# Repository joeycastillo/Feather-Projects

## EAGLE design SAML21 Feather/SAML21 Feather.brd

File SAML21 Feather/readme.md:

# SAML21 Feather

Abandoned halfway through. The useful thing here would be the battery backup for the RTC. 

An interesting idea, but ultimately the SAMD series is so well supported I went back to designing a SAMD board with a battery-backed RTC.

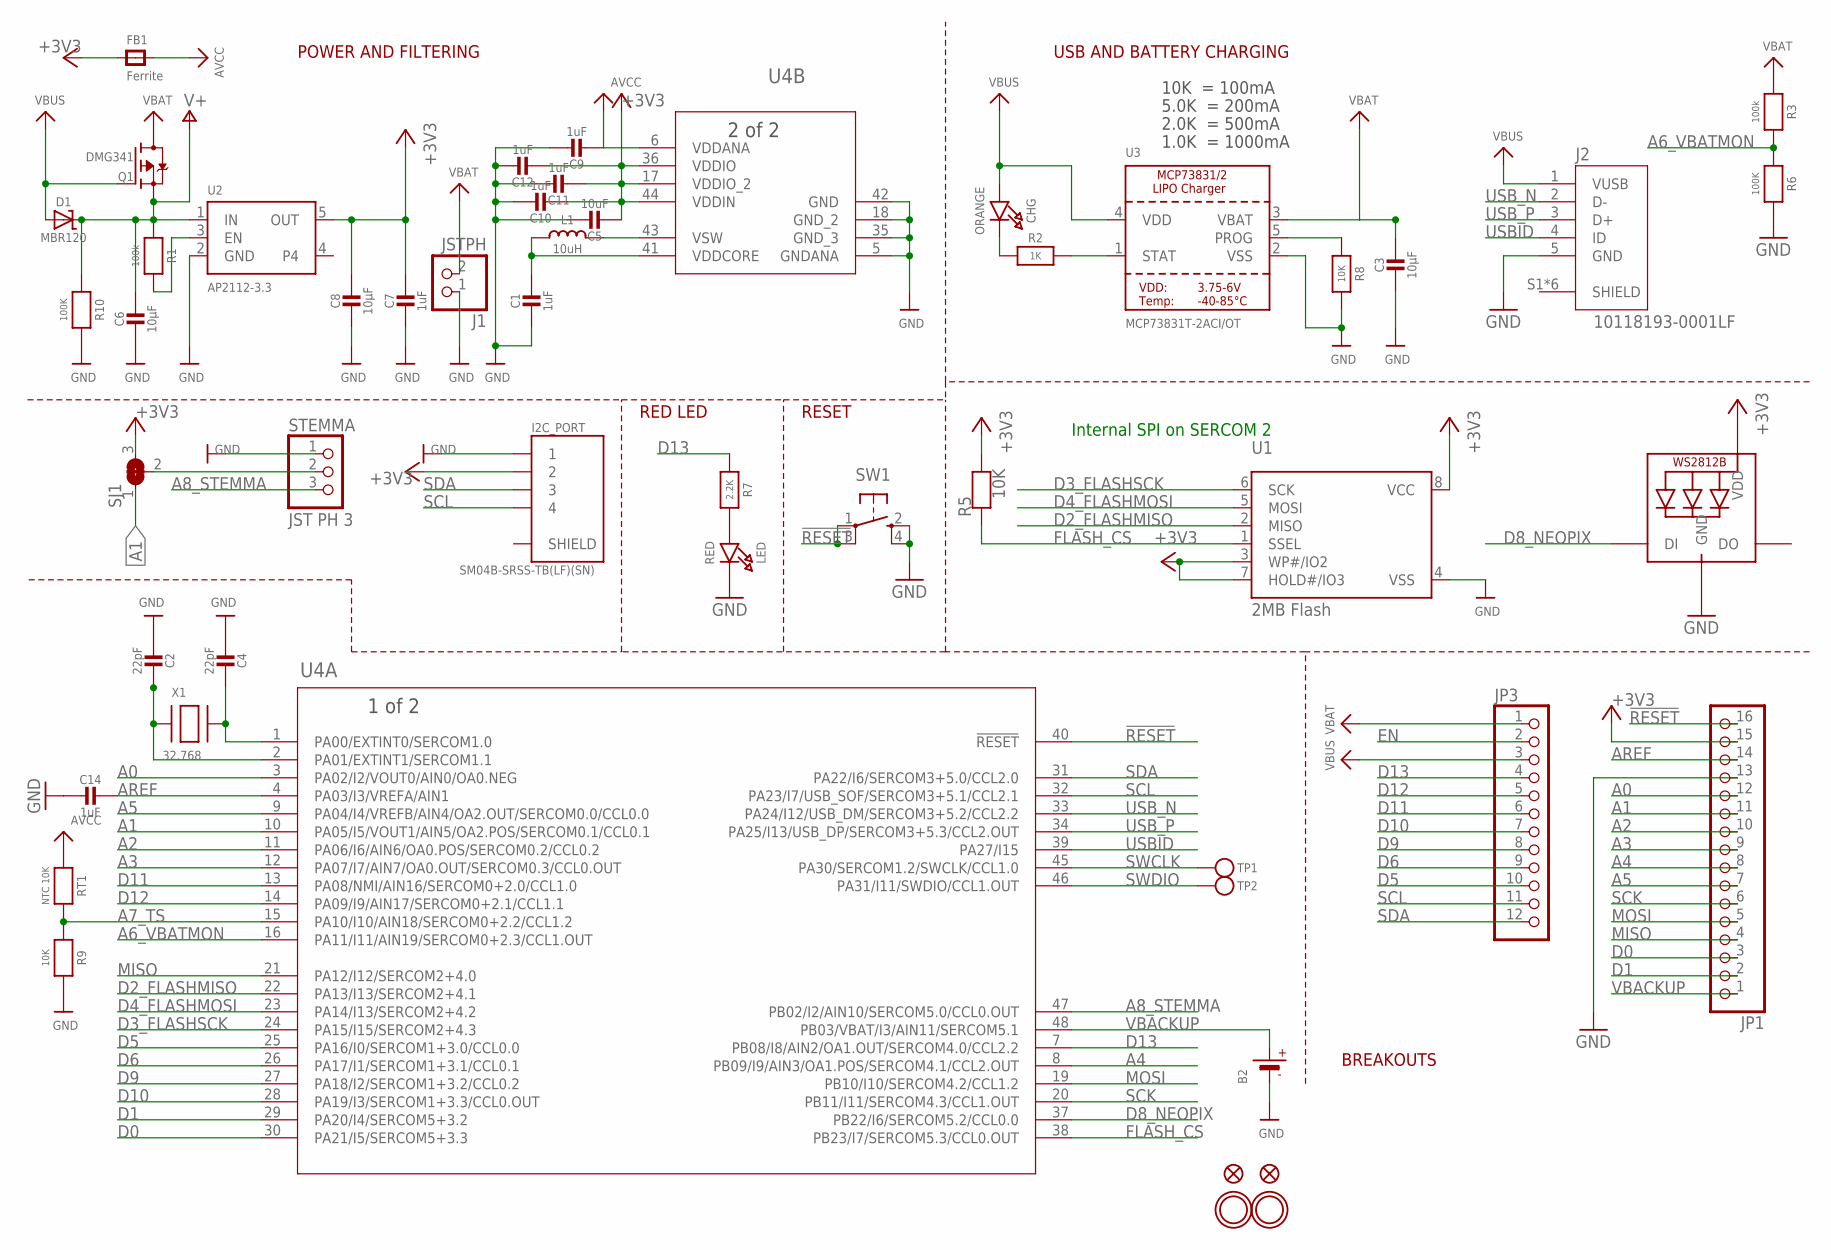
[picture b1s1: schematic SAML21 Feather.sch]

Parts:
B2: CR1220; CR1220-2
C1, C7, C9, C10, C11, C12, C14: 1uF; 0805-NO
C2, C4: 22pF; 0805-NO
C3, C6, C8: 10µF; 0805-NO
C5: 10uF; 0805-NO
CHG: ORANGE; CHIPLED_0805_NOOUTLINE
D1: MBR120; SOD-123
FB1: Ferrite; 0805
I2C_PORT: SM04B-SRSS-TB(LF)(SN); JST_SM04B-SRSS-TB(LF)(SN)
J1: JSTPH; JSTPH2
J2: 10118193-0001LF; FCI_10118193-0001LF
JP1: HEADER-1X16ROUND; 1X16_ROUND
JP3: HEADER-1X12; 1X12_ROUND
L1: 10uH; MICROBUILDER_INDUCTOR_4X4MM_NR401_BIGPADS
LED: RED; CHIPLED_0805_NOOUTLINE
NEOPIX: WS2812B3535; LED3535
Q1: DMG341; SOT23-R
R1: 100k; 0805-NO
R2: 1K; 0805-NO
R3: 100k; 0805_10MGAP
R5, R8, R9: 10K; 0805-NO
R6, R10: 100K; 0805-NO
R7: 2.2K; 0805-NO
RT1: NTC 10K; 0805-NO
SJ1: SOLDERJUMPER_2WAY; SOLDERJUMPER_2WAY_OPEN_NOPASTE
STEMMA: JST PH 3; JSTPH3
SW1: SPST_TACT-KMR2; KMR2
TP1, TP2: TESTPOINTROUND1.5MM; TESTPOINT_ROUND_1.5MM
U1: 2MB Flash; SOIC8_208MIL
U2: AP2112-3.3; SOT23-5
U3: MCP73831T-2ACI/OT; SOT23-5
U4: ATSAML21G16B-ANT; TQFP48_7X7MC
U$31, U$32: MOUNTINGHOLE2.5; MOUNTINGHOLE_2.5_PLATED
U$34, U$35: FIDUCIAL""; FIDUCIAL_1MM
X1: 32.768; XTAL3215

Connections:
!RESET: JP1.16, SW1.1, SW1.3 (P1), U4.40 (!RESET)
+3V3: C5.2, C7.1, C8.1, C10.2, C11.2, C12.2, FB1.1, I2C_PORT.2, JP1.15, NEOPIX.2 (VDD), R5.2, SJ1.3, U1.3 (WP#/IO2), U1.7 (HOLD#/IO3), U1.8 (VCC), U2.5 (OUT), U4.17 (VDDIO_2), U4.36 (VDDIO), U4.44 (VDDIN)
A0: JP1.12, U4.3 (PA02/I2/VOUT0/AIN0/OA0.NEG)
A1: JP1.11, SJ1.1, U4.10 (PA05/I5/VOUT1/AIN5/OA2.POS/SERCOM0.1/CC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)
A2: JP1.10, U4.11 (PA06/I6/AIN6/OA0.POS/SERCOM0.2/CCL0.2)
A3: JP1.9, U4.12 (PA07/I7/AIN7/OA0.OUT/SERCOM0.3/CCL0.OUT)
A4: JP1.8, U4.8 (PB09/I9/AIN3/OA1.POS/SERCOM4.1/CCL2.OUT)
A5: JP1.7, U4.9 (PA04/I4/VREFB/AIN4/OA2.OUT/SERCOM0.0/CC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)
A6_VBATMON: R3.2, R6.1, U4.16 (PA11/I11/AIN19/SERCOM0+2.3/CCL1.OUT)
A7_TS: R9.1, RT1.2, U4.15 (PA10/I10/AIN18/SERCOM0+2.2/CCL1.2)
A8_STEMMA: STEMMA.3, U4.47 (PB02/I2/AIN10/SERCOM5.0/CCL0.OUT)
AREF: C14.1, JP1.14, U4.4 (PA03/I3/VREFA/AIN1)
AVCC: C9.2, FB1.2, RT1.1, U4.6 (VDDANA)
D0: JP1.3, U4.30 (PA21/I5/SERCOM5+3.3)
D1: JP1.2, U4.29 (PA20/I4/SERCOM5+3.2)
D2_FLASHMISO: U1.2 (MISO), U4.22 (PA13/I13/SERCOM2+4.1)
D3_FLASHSCK: U1.6 (SCK), U4.24 (PA15/I15/SERCOM2+4.3)
D4_FLASHMOSI: U1.5 (MOSI), U4.23 (PA14/I13/SERCOM2+4.2)
D5: JP3.10, U4.25 (PA16/I0/SERCOM1+3.0/CCL0.0)
D6: JP3.9, U4.26 (PA17/I1/SERCOM1+3.1/CCL0.1)
D8_NEOPIX: NEOPIX.1 (DI), U4.37 (PB22/I6/SERCOM5.2/CCL0.0)
D9: JP3.8, U4.27 (PA18/I2/SERCOM1+3.2/CCL0.2)
D10: JP3.7, U4.28 (PA19/I3/SERCOM1+3.3/CCL0.OUT)
D11: JP3.6, U4.13 (PA08/NMI/AIN16/SERCOM0+2.0/CCL1.0)
D12: JP3.5, U4.14 (PA09/I9/AIN17/SERCOM0+2.1/CCL1.1)
D13: JP3.4, R7.1, U4.7 (PB08/I8/AIN2/OA1.OUT/SERCOM4.0/CCL2.2)
EN: JP3.2, R1.2, U2.3 (EN)
FLASH_CS: R5.1, U1.1 (SSEL), U4.38 (PB23/I7/SERCOM5.3/CCL0.OUT)
GND: B2.-, C1.2, C2.2, C3.2, C4.2, C5.1, C6.2, C7.2, C8.2, C9.1, C10.1, C11.1, C12.1, C14.2, I2C_PORT.1, J1.1, J2.5 (GND), JP1.13, LED.C, NEOPIX.4 (GND), R6.2, R8.2, R9.2, R10.2, STEMMA.1, SW1.2 (S), SW1.4 (S1), U1.4 (VSS), U2.2 (GND), U3.2 (VSS), U4.5 (GNDANA), U4.18 (GND_2), U4.35 (GND_3), U4.42 (GND)
MISO: JP1.4, U4.21 (PA12/I12/SERCOM2+4.0)
MOSI: JP1.5, U4.19 (PB10/I10/SERCOM4.2/CCL1.2)
unnamed: CHG.C, R2.1
unnamed: LED.A, R7.2
unnamed: SJ1.2, STEMMA.2
PROG: R8.1, U3.5 (PROG)
SCK: JP1.6, U4.20 (PB11/I11/SERCOM4.3/CCL1.OUT)
SCL: I2C_PORT.4, JP3.11, U4.32 (PA23/I7/USB_SOF/SERCOM3+5.1/CCL2.1)
SDA: I2C_PORT.3, JP3.12, U4.31 (PA22/I6/SERCOM3+5.0/CCL2.0)
STAT: R2.2, U3.1 (STAT)
SWCLK: TP1.P$1, U4.45 (PA30/SERCOM1.2/SWCLK/CCL1.0)
SWDIO: TP2.P$1, U4.46 (PA31/I11/SWDIO/CCL1.OUT)
USBID: J2.4 (ID), U4.39 (PA27/I15)
USB_N: J2.2 (D-), U4.33 (PA24/I12/USB_DM/SERCOM3+5.2/CCL2.2)
USB_P: J2.3 (D+), U4.34 (PA25/I13/USB_DP/SERCOM3+5.3/CCL2.OUT)
V+: C6.1, D1.C, Q1.2 (S), R1.1, R10.1, U2.1 (IN)
VBACKUP: B2.+, JP1.1, U4.48 (PB03/VBAT/I3/AIN11/SERCOM5.1)
VBAT: C3.1, J1.2, JP3.1, Q1.3 (D), R3.1, U3.3 (VBAT)
VBUS: CHG.A, D1.A, J2.1 (VUSB), JP3.3, Q1.1 (G), U3.4 (VDD)
VDDCORE: C1.1, L1.P$1 (1), U4.41 (VDDCORE)
VSW: L1.P$2 (2), U4.43 (VSW)
XIN32: C4.1, U4.1 (PA00/EXTINT0/SERCOM1.0), X1.P$2
XOUT32: C2.1, U4.2 (PA01/EXTINT1/SERCOM1.1), X1.P$1

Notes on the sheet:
POWER AND FILTERING
RESET
10K = 100mA
5.0K = 200mA
2.0K = 500mA
1.0K = 1000mA
USB AND BATTERY CHARGING
BREAKOUTS
RED LED
Internal SPI on SERCOM 2

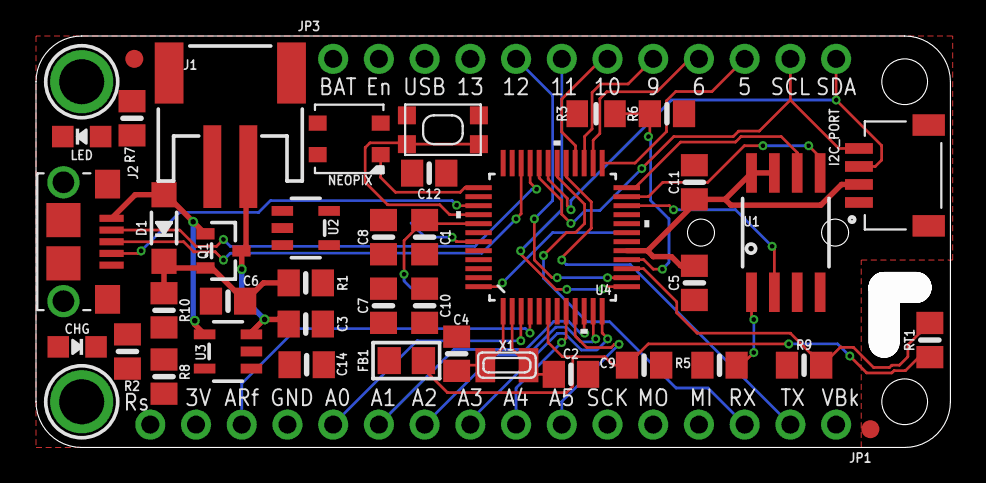
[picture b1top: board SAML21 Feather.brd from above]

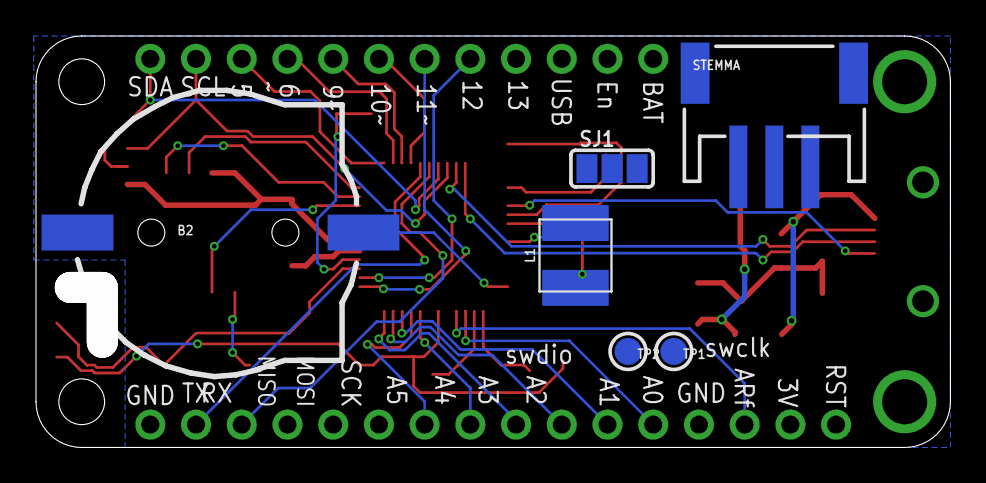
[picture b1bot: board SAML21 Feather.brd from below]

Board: 2 copper layers, 50.8 x 22.9 mm, 50 parts (6 on the bottom side), 52 nets.

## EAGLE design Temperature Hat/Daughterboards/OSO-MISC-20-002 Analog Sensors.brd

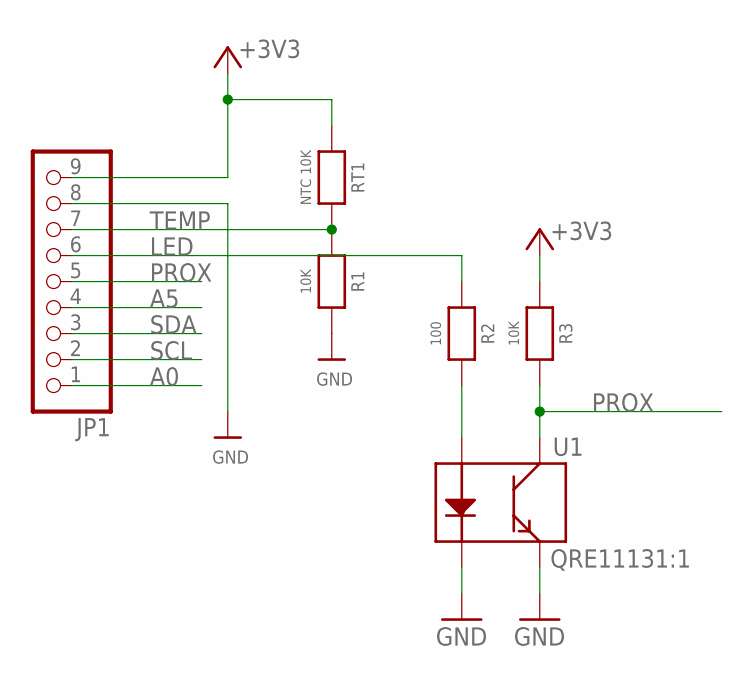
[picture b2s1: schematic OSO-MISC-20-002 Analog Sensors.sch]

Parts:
JP1: HEADER-1X9_JSTSH; JST_SH9
R1, R3: 10K; 0805-NO
R2: 100; 0805-NO
RT1: NTC 10K; 0805-NO
U1: QRE11131:1; QRE1113-1:1

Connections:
+3V3: JP1.9, R3.1, RT1.1
A0: JP1.1
A5: JP1.4
GND: JP1.8, R1.2, U1.2 (K), U1.4 (E)
LED: JP1.6, R2.1
unnamed: R2.2, U1.1 (A)
PROX: JP1.5, R3.2, U1.3 (C)
SCL: JP1.2
SDA: JP1.3
TEMP: JP1.7, R1.1, RT1.2

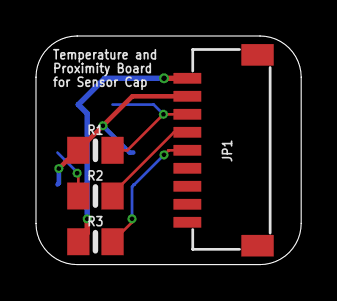
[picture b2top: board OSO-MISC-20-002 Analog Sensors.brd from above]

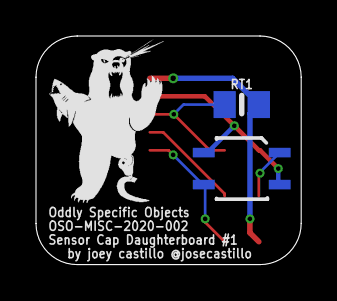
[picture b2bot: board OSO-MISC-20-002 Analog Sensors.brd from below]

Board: 2 copper layers, 14.7 x 12.7 mm, 7 parts (3 on the bottom side), 6 nets.

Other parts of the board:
U$2: OSO_BEAR_250X360MIL_1000DPI

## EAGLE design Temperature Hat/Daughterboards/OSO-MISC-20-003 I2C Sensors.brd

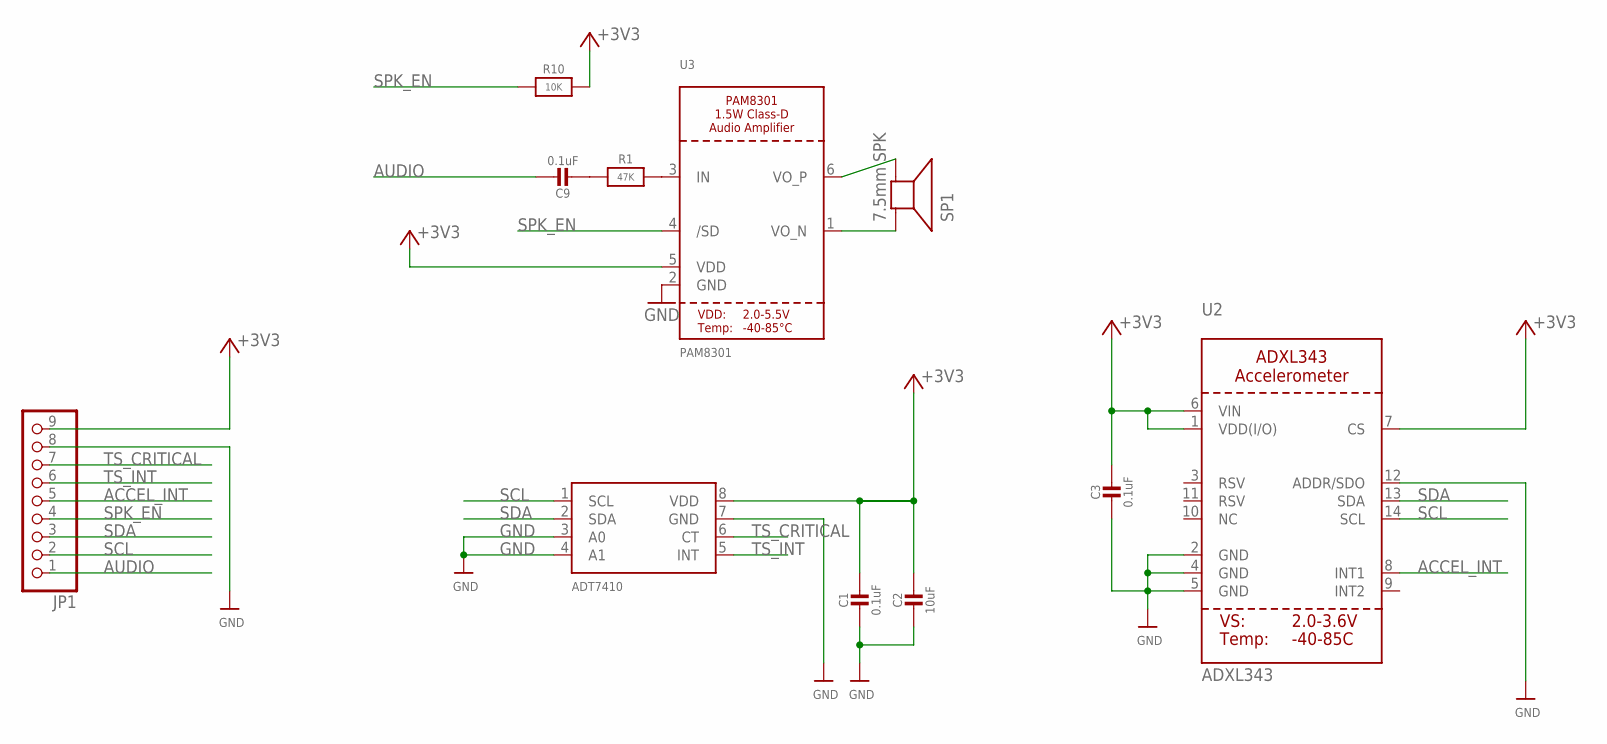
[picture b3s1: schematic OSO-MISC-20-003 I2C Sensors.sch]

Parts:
C1, C3, C9: 0.1uF; 0805-NO
C2: 10uF; 0805-NO
JP1: HEADER-1X9_JSTSH; JST_SH9
R1: 47K; 0805-NO
R10: 10K; 0805-NO
SP1: 7.5mm SPK; BUZZER_SMT_5MM
U1: ADT7410; SOIC8_150MIL
U2: ADXL343; LGA14
U3: PAM8301; SOT23-6

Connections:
+3V3: C1.1, C2.1, C3.1, JP1.9, R10.2, U1.8 (VDD), U2.1 (VDD(I/O)), U2.6 (VIN), U2.7 (CS), U3.5 (VDD)
ACCEL_INT: JP1.5, U2.8 (INT1)
AUDIO: C9.1, JP1.1
GND: C1.2, C2.2, C3.2, JP1.8, U1.3 (A0), U1.4 (A1), U1.7 (GND), U2.2 (GND), U2.4 (GND), U2.5 (GND), U2.12 (ADDR/SDO), U3.2 (GND)
unnamed: C9.2, R1.1
unnamed: R1.2, U3.3 (IN)
SCL: JP1.2, U1.1 (SCL), U2.14 (SCL)
SDA: JP1.3, U1.2 (SDA), U2.13 (SDA)
SPK_EN: JP1.4, R10.1, U3.4 (/SD)
SPK_N: SP1.+, U3.1 (VO_N)
SPK_P: SP1.-, U3.6 (VO_P)
TS_CRITICAL: JP1.7, U1.6 (CT)
TS_INT: JP1.6, U1.5 (INT)

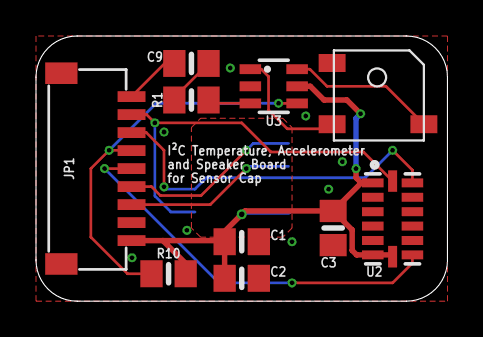
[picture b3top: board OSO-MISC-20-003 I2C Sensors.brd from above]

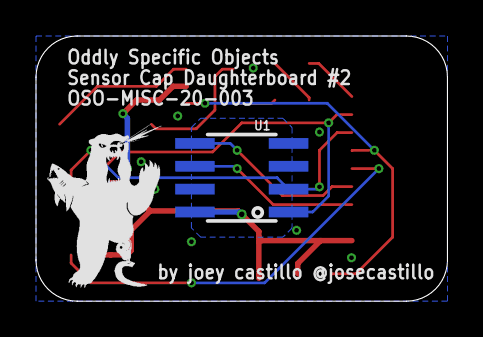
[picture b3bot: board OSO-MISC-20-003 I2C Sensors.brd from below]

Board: 2 copper layers, 22.9 x 14.7 mm, 12 parts (2 on the bottom side), 13 nets.

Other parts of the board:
U$3: OSO_BEAR_250X360MIL_1000DPI

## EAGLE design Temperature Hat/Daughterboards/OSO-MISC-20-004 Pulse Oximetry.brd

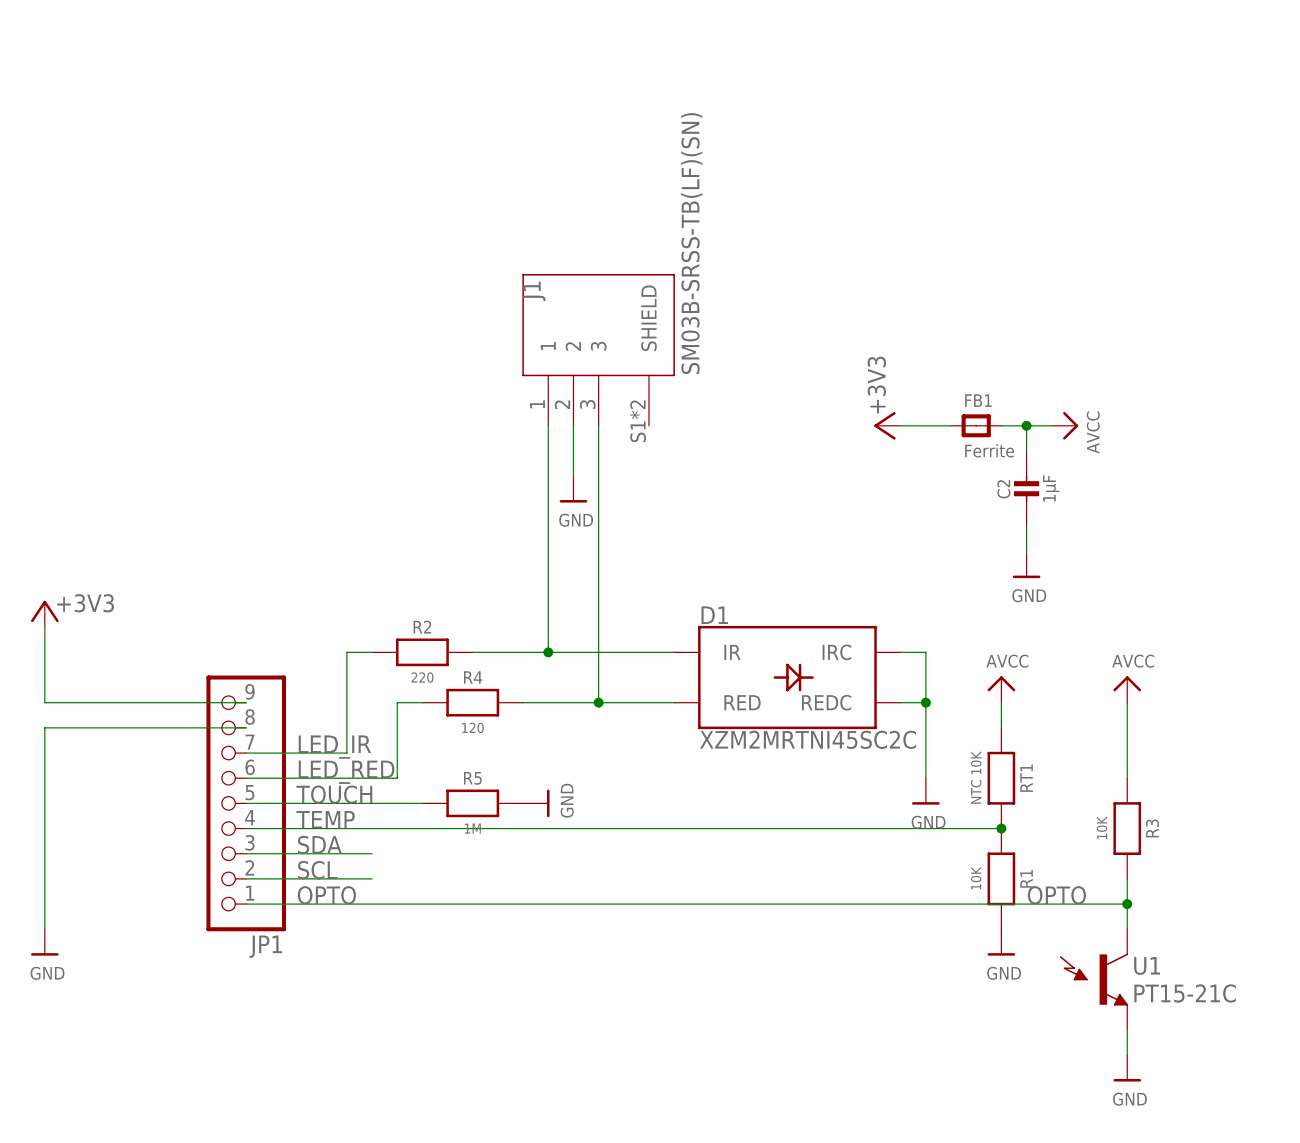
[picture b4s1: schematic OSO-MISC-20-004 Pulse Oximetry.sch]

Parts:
C2: 1µF; 0805-NO
D1: XZM2MRTNI45SC2C; PLCC4SMDLED
FB1: Ferrite; 0805
J1: SM03B-SRSS-TB(LF)(SN); JST_SM03B-SRSS-TB(LF)(SN)
JP1: HEADER-1X9_JSTSH; JST_SH9
R1, R3: 10K; 0805-NO
R2: 220; 0805-NO
R4: 120; 0805-NO
R5: 1M; 0805_10MGAP
RT1: NTC 10K; 0805-NO
U1: PT15-21C; LED-1206

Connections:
+3V3: FB1.1, JP1.9
AVCC: C2.1, FB1.2, R3.1, RT1.1
GND: C2.2, D1.1 (REDC), D1.3 (IRC), J1.2, JP1.8, R1.2, R5.2, U1.C (E1)
IR_LIM: D1.4 (IR), J1.1, R2.2
LED_IR: JP1.7, R2.1
LED_RED: JP1.6, R4.1
OPTO: JP1.1, R3.2, U1.A (C1)
RED_LIM: D1.2 (RED), J1.3, R4.2
SCL: JP1.2
SDA: JP1.3
TEMP: JP1.4, R1.1, RT1.2
TOUCH: JP1.5, R5.1

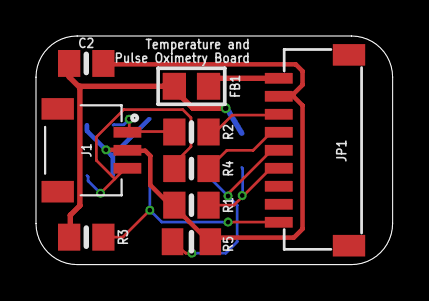
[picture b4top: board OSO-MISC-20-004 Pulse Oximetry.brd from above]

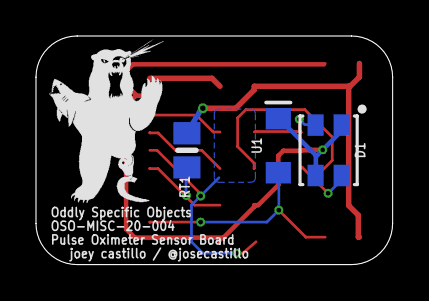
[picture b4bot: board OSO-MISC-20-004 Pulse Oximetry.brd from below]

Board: 2 copper layers, 19.8 x 12.7 mm, 13 parts (4 on the bottom side), 10 nets.

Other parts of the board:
U$2: OSO_BEAR_250X360MIL_1000DPI

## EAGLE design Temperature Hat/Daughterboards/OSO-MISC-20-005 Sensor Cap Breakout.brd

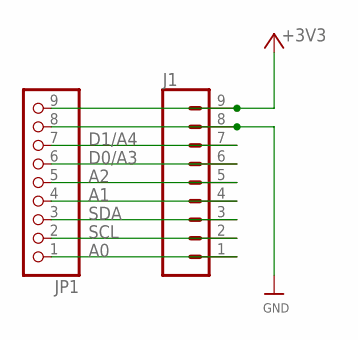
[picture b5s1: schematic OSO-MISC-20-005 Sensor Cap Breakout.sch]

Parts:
J1: CONN_09NO_SILK; 1X09_NO_SILK
JP1: HEADER-1X9_JSTSH; JST_SH9

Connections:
+3V3: J1.9, JP1.9
A0: J1.1, JP1.1
A1: J1.4, JP1.4
A2: J1.5, JP1.5
D0/A3: J1.6, JP1.6
D1/A4: J1.7, JP1.7
GND: J1.8, JP1.8
SCL: J1.2, JP1.2
SDA: J1.3, JP1.3

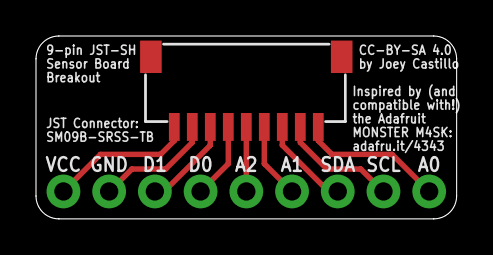
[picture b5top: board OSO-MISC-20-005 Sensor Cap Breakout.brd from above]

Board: 2 copper layers, 23.4 x 10.2 mm, 3 parts (1 on the bottom side), 9 nets.

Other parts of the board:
U$1: OSO_WORDMARK_ONELINE_725MIL_1000DPI

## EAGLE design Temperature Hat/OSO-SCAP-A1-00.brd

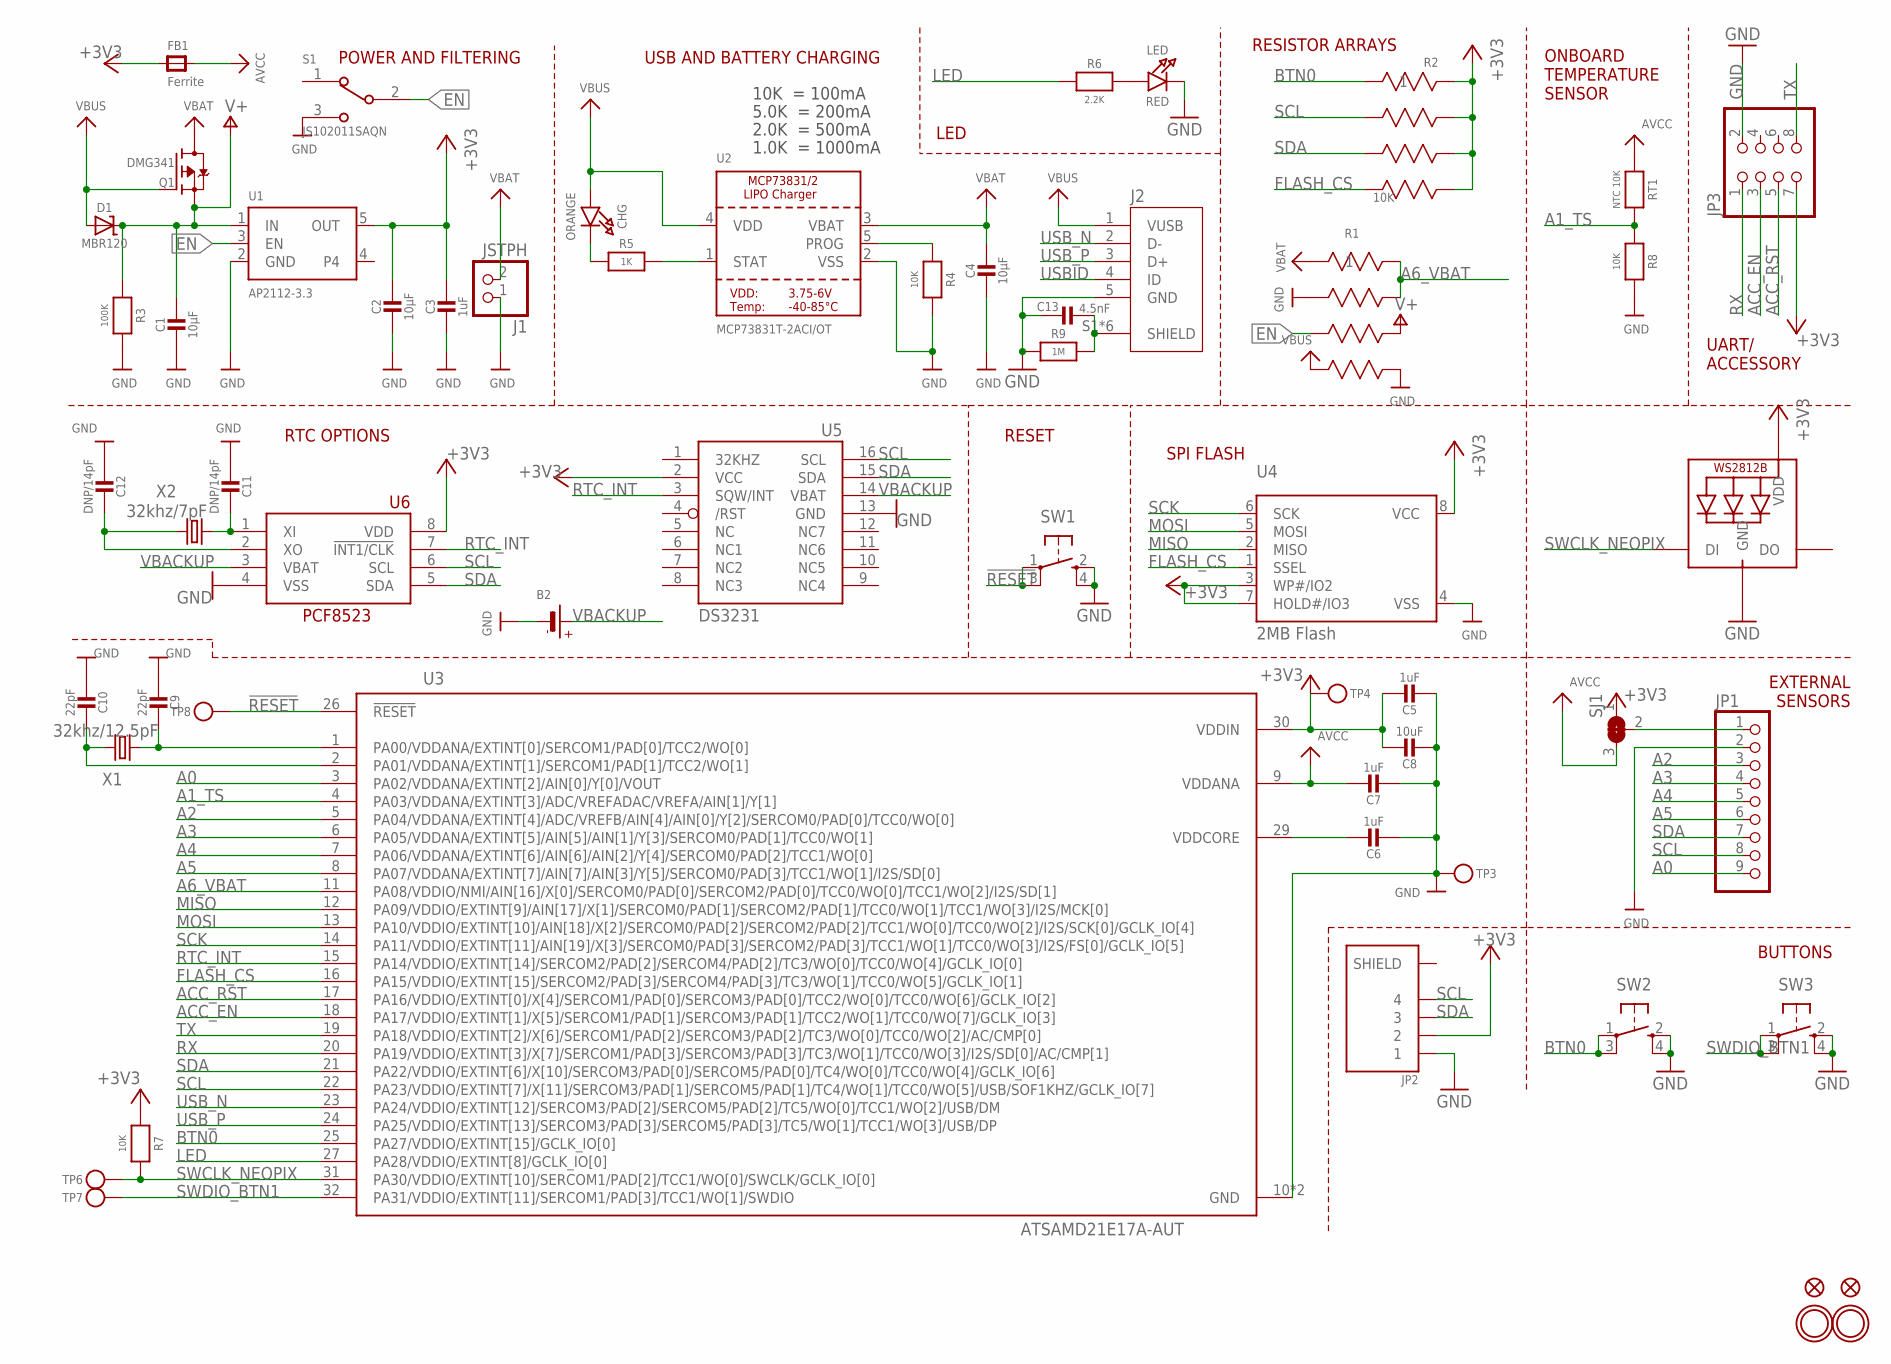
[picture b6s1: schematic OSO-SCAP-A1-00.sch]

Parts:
B2: CR1220; CR1220-2
C1: 10µF; 0805_10MGAP
C2, C4: 10µF; 0805-NO
C3, C5, C6, C7: 1uF; 0805-NO
C8: 10uF; 0805-NO
C9, C10: 22pF; 0805-NO
C11, C12: DNP/14pF; 0805_10MGAP
C13: 4.5nF; 0805-NO
CHG: ORANGE; CHIPLED_0805_NOOUTLINE
D1: MBR120; SOD-123
FB1: Ferrite; 0805
J1: JSTPH; JSTPH2
J2: 10118193-0001LF; FCI_10118193-0001LF
JP1: HEADER-1X9_JSTSH; JST_SH9
JP2: SM04B-SRSS-TB(LF)(SN); JST_SM04B-SRSS-TB(LF)(SN)
JP3: PINHD-2X4SMT; PINHD_2X4_SMT
LED: RED; CHIPLED_0805_NOOUTLINE
NEOPIX: WS2812B_4020
Q1: DMG341; SOT23-R
R1: 100K; EXBV8V
R2: 10K; EXBV8V
R3: 100K; 0805-NO
R4, R7, R8: 10K; 0805-NO
R5: 1K; 0805-NO
R6: 2.2K; 0805-NO
R9: 1M; 0805-NO
RT1: NTC 10K; 0805-NO
S1: JS102011SAQN; SW_JS102011SAQN
SJ1: SOLDERJUMPER_2WAY; SOLDERJUMPER_2WAY_OPEN_NOPASTE
SW1, SW2, SW3: SPST_TACT-KMR2; KMR2
TP3, TP4, TP6, TP7, TP8: TESTPOINTROUND2MMNO; TESTPOINT_ROUND_2MM_NO
U1: AP2112-3.3; SOT23-5
U2: MCP73831T-2ACI/OT; SOT23-5
U3: ATSAMD21E17A-AUT; QFP80P900X900X120-32N
U4: 2MB Flash; SOIC8_208MIL
U5: DS3231/SO; SO16W
U6: PCF8523T; SOIC8_150MIL
U$31, U$32: MOUNTINGHOLE2.5; MOUNTINGHOLE_2.5_PLATED
U$34, U$35: FIDUCIAL""; FIDUCIAL_1MM
X1: 32khz/12.5pF; XTAL-7015
X2: 32khz/7pF; XTAL-7015

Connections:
!RESET: SW1.1, SW1.3 (P1), TP8.P$1, U3.26 (!RESET)
+3V3: C2.1, C3.1, C5.1, C8.1, FB1.1, JP2.2, JP3.7, NEOPIX.2 (VDD), R2.5, R2.6, R2.7, R2.8, R7.1, SJ1.1, TP4.P$1, U1.5 (OUT), U3.30 (VDDIN), U4.3 (WP#/IO2), U4.7 (HOLD#/IO3), U4.8 (VCC), U5.2 (VCC), U6.8 (VDD)
A0: JP1.9, U3.3 (PA02/VDDANA/EXTINT[2]/AIN[0]/Y[0]/VOUT)
A1_TS: R8.1, RT1.2, U3.4 (PA03/VDDANA/EXTINT[3]/ADC/VREFADAC/VREF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)
A2: JP1.3, U3.5 (PA04/VDDANA/EXTINT[4]/ADC/VREFB/AIN[4]/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)
A3: JP1.4, U3.6 (PA05/VDDANA/EXTINT[5]/AIN[5]/AIN[1]/Y[3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)
A4: JP1.5, U3.7 (PA06/VDDANA/EXTINT[6]/AIN[6]/AIN[2]/Y[4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)
A5: JP1.6, U3.8 (PA07/VDDANA/EXTINT[7]/AIN[7]/AIN[3]/Y[5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)
A6_VBAT: R1.7, R1.8, U3.11 (PA08/VDDIO/NMI/AIN[16]/X[0]/SERCOM0/PAD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)
ACC_EN: JP3.3, U3.18 (PA17/VDDIO/EXTINT[1]/X[5]/SERCOM1/PAD[1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)
ACC_RST: JP3.5, U3.17 (PA16/VDDIO/EXTINT[0]/X[4]/SERCOM1/PAD[0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)
AVCC: C7.1, FB1.2, RT1.1, SJ1.3, U3.9 (VDDANA)
BTN0: R2.1, SW2.1, SW2.3 (P1), U3.25 (PA27/VDDIO/EXTINT[15]/GCLK_IO[0])
EN: R1.3, S1.2, U1.3 (EN)
FLASH_CS: R2.4, U3.16 (PA15/VDDIO/EXTINT[15]/SERCOM2/PAD[3]/SE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), U4.1 (SSEL)
GND: B2.-, C1.2, C2.2, C3.2, C4.2, C5.2, C6.2, C7.2, C8.2, C9.2, C10.2, C11.2, C12.2, C13.1, J1.1, J2.5 (GND), JP1.2, JP2.1, JP3.2, LED.C, NEOPIX.4 (GND), R1.2, R1.5, R3.2, R4.2, R8.2, R9.1, S1.3, SW1.2 (S), SW1.4 (S1), SW2.2 (S), SW2.4 (S1), SW3.2 (S), SW3.4 (S1), TP3.P$1, U1.2 (GND), U2.2 (VSS), U3.10 (GND), U3.28 (GND), U4.4 (VSS), U5.13 (GND), U6.4 (VSS)
LED: R6.1, U3.27 (PA28/VDDIO/EXTINT[8]/GCLK_IO[0])
MISO: U3.12 (PA09/VDDIO/EXTINT[9]/AIN[17]/X[1]/SERCO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), U4.2 (MISO)
MOSI: U3.13 (PA10/VDDIO/EXTINT[10]/AIN[18]/X[2]/SERC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), U4.5 (MOSI)
unnamed: CHG.C, R5.1
unnamed: LED.A, R6.2
POWER_OUT: JP1.1, SJ1.2
PROG: R4.1, U2.5 (PROG)
RTC_INT: U3.15 (PA14/VDDIO/EXTINT[14]/SERCOM2/PAD[2]/SE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), U5.3 (SQW/INT), U6.7 (!INT1/CLK)
RX: JP3.1, U3.20 (PA19/VDDIO/EXTINT[3]/X[7]/SERCOM1/PAD[3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)
SCK: U3.14 (PA11/VDDIO/EXTINT[11]/AIN[19]/X[3]/SERC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), U4.6 (SCK)
SCL: JP1.8, JP2.4, R2.2, U3.22 (PA23/VDDIO/EXTINT[7]/X[11]/SERCOM3/PAD[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), U5.16 (SCL), U6.6 (SCL)
SDA: JP1.7, JP2.3, R2.3, U3.21 (PA22/VDDIO/EXTINT[6]/X[10]/SERCOM3/PAD[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), U5.15 (SDA), U6.5 (SDA)
SHIELD: C13.2, J2.S1 (SHIELD), J2.S2 (SHIELD), J2.S3 (SHIELD), J2.S4 (SHIELD), J2.S5 (SHIELD), J2.S6 (SHIELD), R9.2
STAT: R5.2, U2.1 (STAT)
SWCLK_NEOPIX: NEOPIX.1 (DI), R7.2, TP6.P$1, U3.31 (PA30/VDDIO/EXTINT[10]/SERCOM1/PAD[2]/TC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)
SWDIO_BTN1: SW3.1, SW3.3 (P1), TP7.P$1, U3.32 (PA31/VDDIO/EXTINT[11]/SERCOM1/PAD[3]/TC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)
TX: JP3.8, U3.19 (PA18/VDDIO/EXTINT[2]/X[6]/SERCOM1/PAD[2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)
USBID: J2.4 (ID)
USB_N: J2.2 (D-), U3.23 (PA24/VDDIO/EXTINT[12]/SERCOM3/PAD[2]/SE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)
USB_P: J2.3 (D+), U3.24 (PA25/VDDIO/EXTINT[13]/SERCOM3/PAD[3]/SE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)
V+: C1.1, D1.C, Q1.2 (S), R1.6, R3.1, U1.1 (IN)
VBACKUP: B2.+, U5.14 (VBAT), U6.3 (VBAT)
VBAT: C4.1, J1.2, Q1.3 (D), R1.1, U2.3 (VBAT)
VBUS: CHG.A, D1.A, J2.1 (VUSB), Q1.1 (G), R1.4, U2.4 (VDD)
VDDCORE: C6.1, U3.29 (VDDCORE)
XIN32: C9.1, U3.1 (PA00/VDDANA/EXTINT[0]/SERCOM1/PAD[0]/TC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), X1.1
XIN_RTC: C11.1, U6.1 (XI), X2.1
XOUT32: C10.1, U3.2 (PA01/VDDANA/EXTINT[1]/SERCOM1/PAD[1]/TC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), X1.4 (2)
XOUT_RTC: C12.1, U6.2 (XO), X2.4 (2)

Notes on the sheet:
POWER AND FILTERING
RESET
10K = 100mA
5.0K = 200mA
2.0K = 500mA
1.0K = 1000mA
USB AND BATTERY CHARGING
LED
ONBOARD TEMPERATURE SENSOR
UART/ ACCESSORY
BUTTONS
EXTERNAL SENSORS
SPI FLASH
RTC OPTIONS
RESISTOR ARRAYS

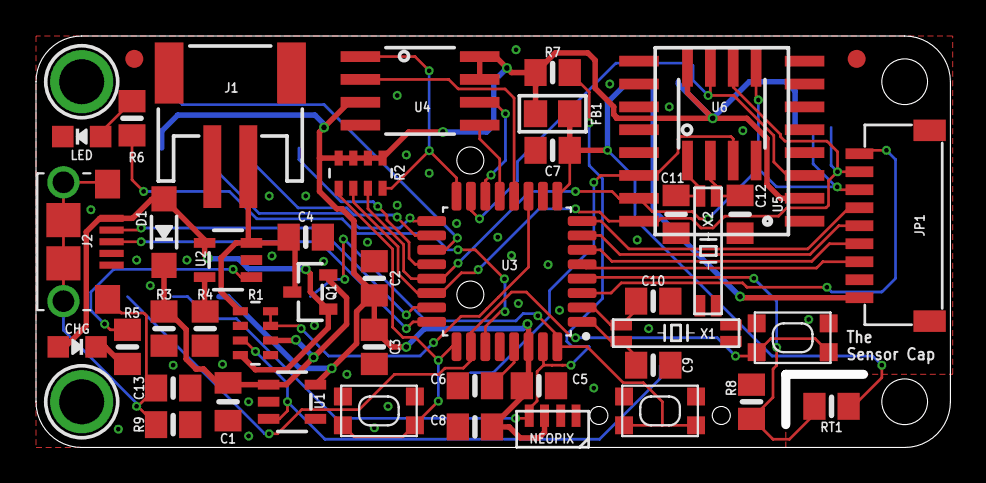
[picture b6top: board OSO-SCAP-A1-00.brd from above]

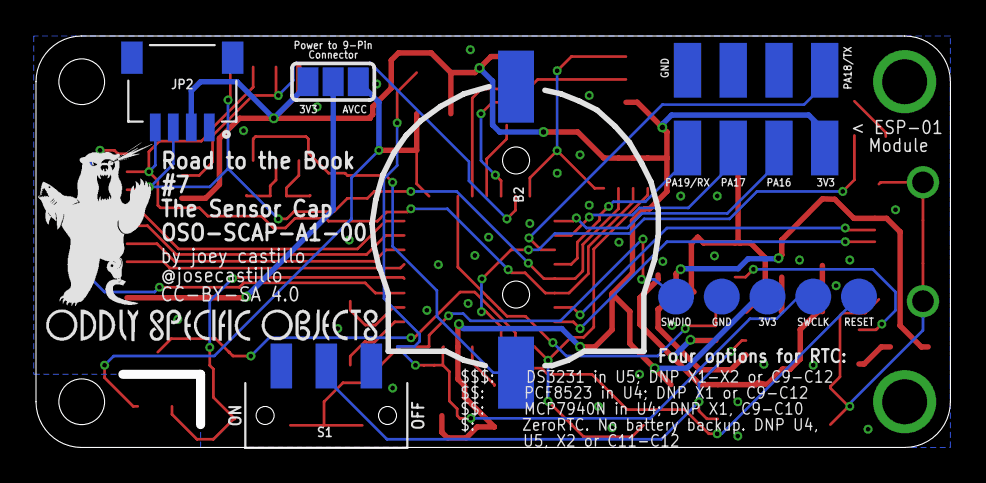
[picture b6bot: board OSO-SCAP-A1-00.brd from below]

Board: 2 copper layers, 50.8 x 22.9 mm, 59 parts (12 on the bottom side), 44 nets.

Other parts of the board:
U$24: OSO_WORDMARK_ONELINE_725MIL_1000DPI
U$25: OSO_BEAR_250X360MIL_1000DPI

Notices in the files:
Temperature Hat/Daughterboards/OSO-MISC-20-005 Sensor Cap Breakout.brd:
CC-BY-SA 4.0
parts and their libraries:
microbuilder: This work is placed in the public domain, and may be freely used for commercial and non-commercial work with the following conditions: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
COPYRIGHT: Copyright (C) 2018 Accelerated Designs. All rights reserved
